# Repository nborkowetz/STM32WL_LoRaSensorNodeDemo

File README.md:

# STM32WL LoRaWAN Sensor Node

Low-power LoRaWAN sensor node based on the **STM32WL55**, originally designed as a prototype platform for distributed water-monitoring applications.

The original goal was not to build a complete water-quality instrument around a fixed set of probes, but to validate the **overall sensing and communication architecture** first: a battery-powered node, generic sensor interfaces, LoRaWAN connectivity, a local gateway and a self-hosted backend.

Water monitoring may involve very different sensors and analog front-ends depending on the quantity being measured. For this reason, the sensing layer is intentionally kept generic while the project focuses on validating the reusable parts of the system.

## Concept

The prototype is intended as a test platform for the complete data path:

```text
Sensor / External AFE
        |
   Analog / RS-485
        |
        v
   STM32WL55 Node
        |
      LoRaWAN
        |
        v
   Dragino Gateway
        |
        v
    ChirpStack
        |
       MQTT
        |
        v
   Backend / Web UI
```

The custom node provides a small set of generic interfaces:

- 3× protected and filtered analog inputs
- RS-485 interface
- Switchable 12 V sensor supply
- STM32WL55 integrated Sub-GHz radio
- USB-UART debug interface
- Battery-powered / low-power operation

Sensor-specific amplification, isolation or signal conditioning can be added externally when required.

This allows the LoRaWAN architecture, power-management strategy and backend to be developed independently from the final choice of water-quality sensors.

## Firmware

The firmware is being developed around a low-power, event-driven architecture with:

- periodic sensor acquisition
- timer-triggered ADC sampling with DMA
- digital filtering / processing
- asynchronous UART / RS-485 communication
- sensor power sequencing and warm-up
- deep-sleep and periodic wake-up
- periodic LoRaWAN uplinks
- UART debug console
- error handling and watchdog supervision

Typical measurement cycle:

```text
Sleep -> Sensor ON -> Warm-up -> Acquire -> Process
      -> Sensor OFF -> LoRaWAN TX (if scheduled) -> Sleep
```

Firmware development and LoRaWAN validation are currently performed using an **STM32WL55 development board**. The custom PCB has been designed but has not yet been fabricated.

Synthetic sensor values can be injected during development to validate payload generation and the complete communication path without depending on the final sensing hardware.

## LoRaWAN Infrastructure

A second goal of the project is to make the LoRaWAN test environment **reproducible and easy to deploy**, instead of relying on a manually configured development machine.

The planned local infrastructure consists of:

- Dragino LoRaWAN gateway
- ChirpStack network server
- Mosquitto MQTT broker
- containerized deployment with Docker Compose
- deployment / provisioning scripts
- Python / FastAPI backend for receiving, storing and visualizing measurements

The intended workflow is:

```text
docker compose up
        |
        v
ChirpStack + MQTT services
        |
        v
Automated provisioning
        |
        v
Gateway / device registration
        |
        v
End-to-end LoRaWAN test
```

Configuration files and scripts are kept in the repository so that the test environment can be recreated from a clean machine with minimal manual configuration.

The backend consumes application data exposed by ChirpStack through MQTT; the STM32 node itself only produces the application payload and remains independent from MQTT or the backend implementation.

## Repository Structure

```text
.
├── Hardware/          # KiCad schematic, PCB and documentation
├── Firmware/          # STM32WL55 firmware
├── Infrastructure/    # ChirpStack / MQTT / Docker deployment
├── Tools/             # Python utilities and provisioning tools
└── README.md
```

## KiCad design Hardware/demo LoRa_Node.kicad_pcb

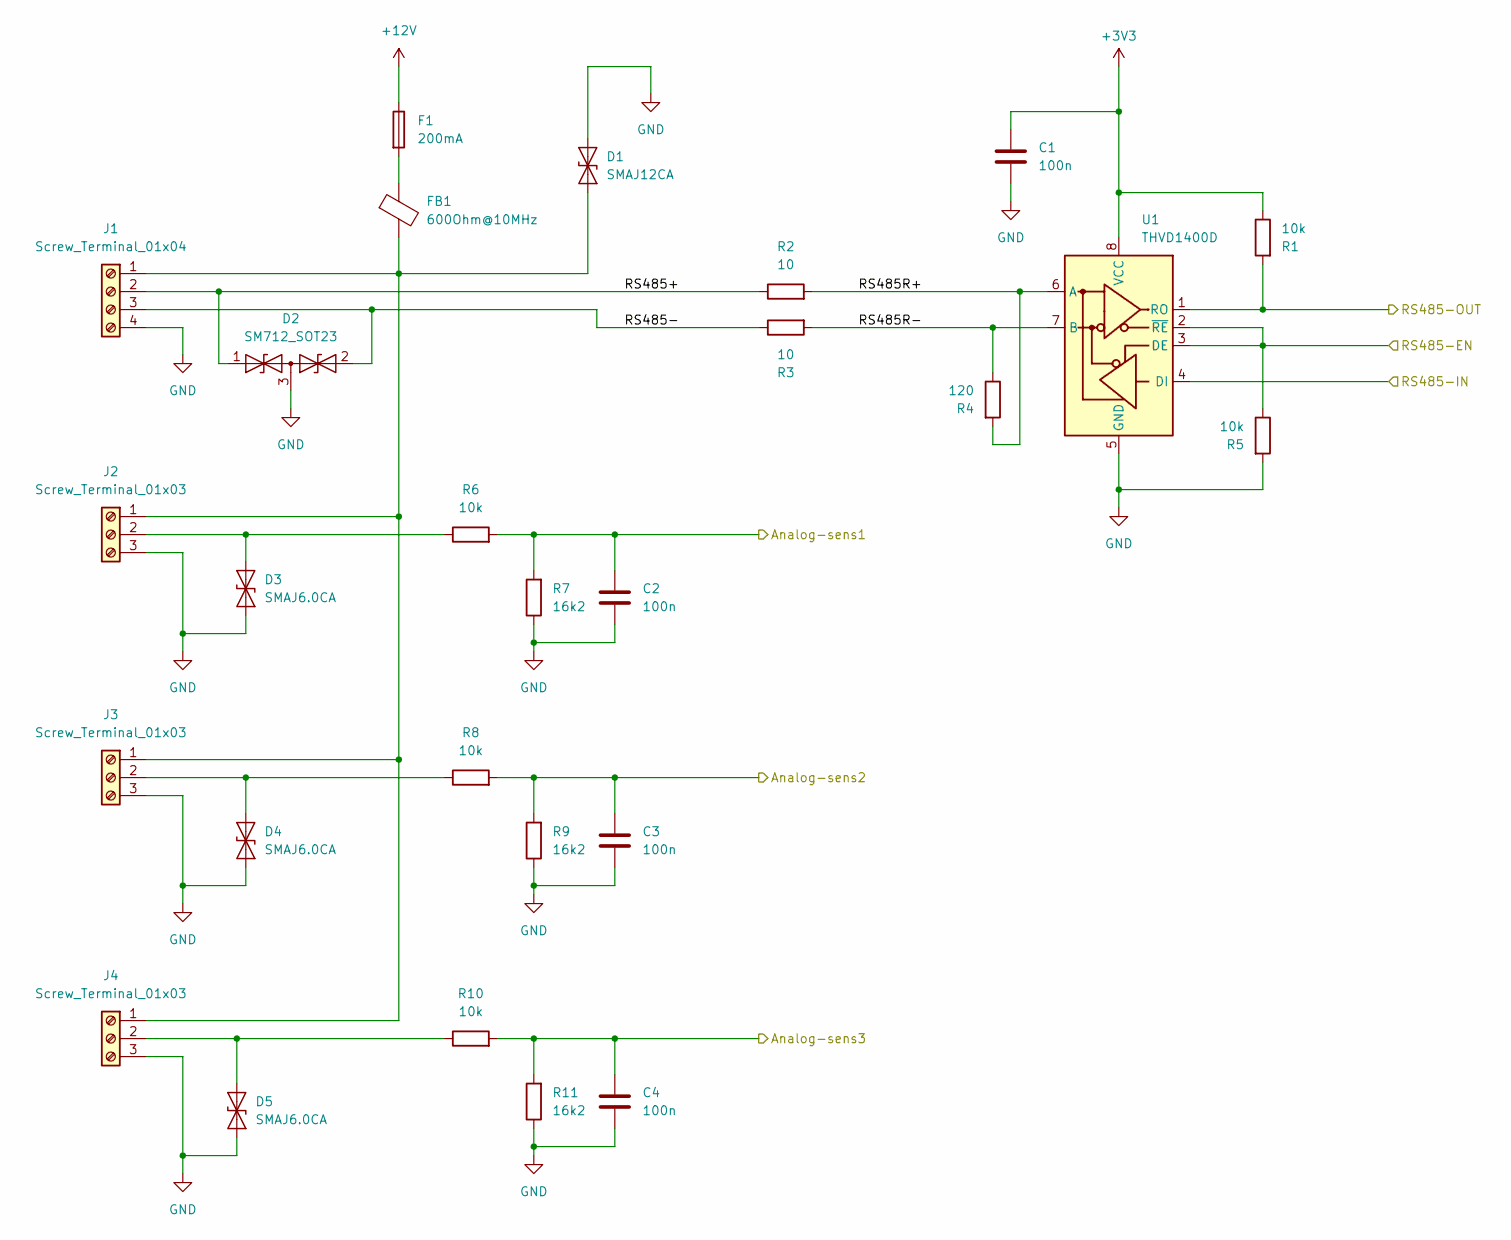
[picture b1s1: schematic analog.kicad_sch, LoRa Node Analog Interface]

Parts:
C1, C2, C3, C4: 100n; C_0603_1608Metric
D1: SMAJ12CA; D_SMA
D2: SM712_SOT23; SOT-23
D3, D4, D5: SMAJ6.0CA; D_SMA
F1: 200mA; Fuse_0805_2012Metric
FB1: 600Ohm@10MHz; L_0603_1608Metric
J1: Screw_Terminal_01x04; TerminalBlock_Phoenix_MKDS-1,5-4-5.08_1x04_P5.08mm_Horizont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
J2, J3, J4: Screw_Terminal_01x03; TerminalBlock_Phoenix_MKDS-1,5-3-5.08_1x03_P5.08mm_Horizont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
R1, R5, R6, R8, R10: 10k; R_0603_1608Metric
R2, R3: 10; R_0603_1608Metric
R4: 120; R_0603_1608Metric
R7, R9, R11: 16k2; R_0603_1608Metric
U1: THVD1400D; SOIC-8_3.9x4.9mm_P1.27mm

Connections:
+3V3: C1.1, R1.1, U1.8 (VCC); also elsewhere on the board
+12V: F1.1; also elsewhere on the board
/MCU/ADC-CH2: C2.1, R6.2, R7.2; also elsewhere on the board
/MCU/ADC-CH3: C3.1, R8.2, R9.2; also elsewhere on the board
/MCU/ADC-CH4: C4.1, R10.2, R11.2; also elsewhere on the board
/MCU/RS485-EN: R5.1, U1.2 (~RE), U1.3 (DE); also elsewhere on the board
/MCU/UART-RX: R1.2, U1.1 (RO); also elsewhere on the board
/MCU/UART-TX: U1.4 (DI); also elsewhere on the board
/analog/RS485+: D2.1 (A1), J1.2, R2.1
/analog/RS485-: D2.2 (A2), J1.3, R3.1
/analog/RS485R+: R2.2, R4.2, U1.6 (A)
/analog/RS485R-: R3.2, R4.1, U1.7 (B)
GND: C1.2, C2.2, C3.2, C4.2, D1.2 (A2), D2.3 (common), D3.1 (A1), D4.1 (A1), D5.1 (A1), J1.4, J2.3, J3.3, J4.3, R5.2, R7.1, R9.1, R11.1, U1.5 (GND); also elsewhere on the board
unnamed: D1.1 (A1), FB1.2, J1.1, J2.1, J3.1, J4.1
unnamed: D3.2 (A2), J2.2, R6.1
unnamed: D4.2 (A2), J3.2, R8.1
unnamed: D5.2 (A2), J4.2, R10.1
unnamed: F1.2, FB1.1

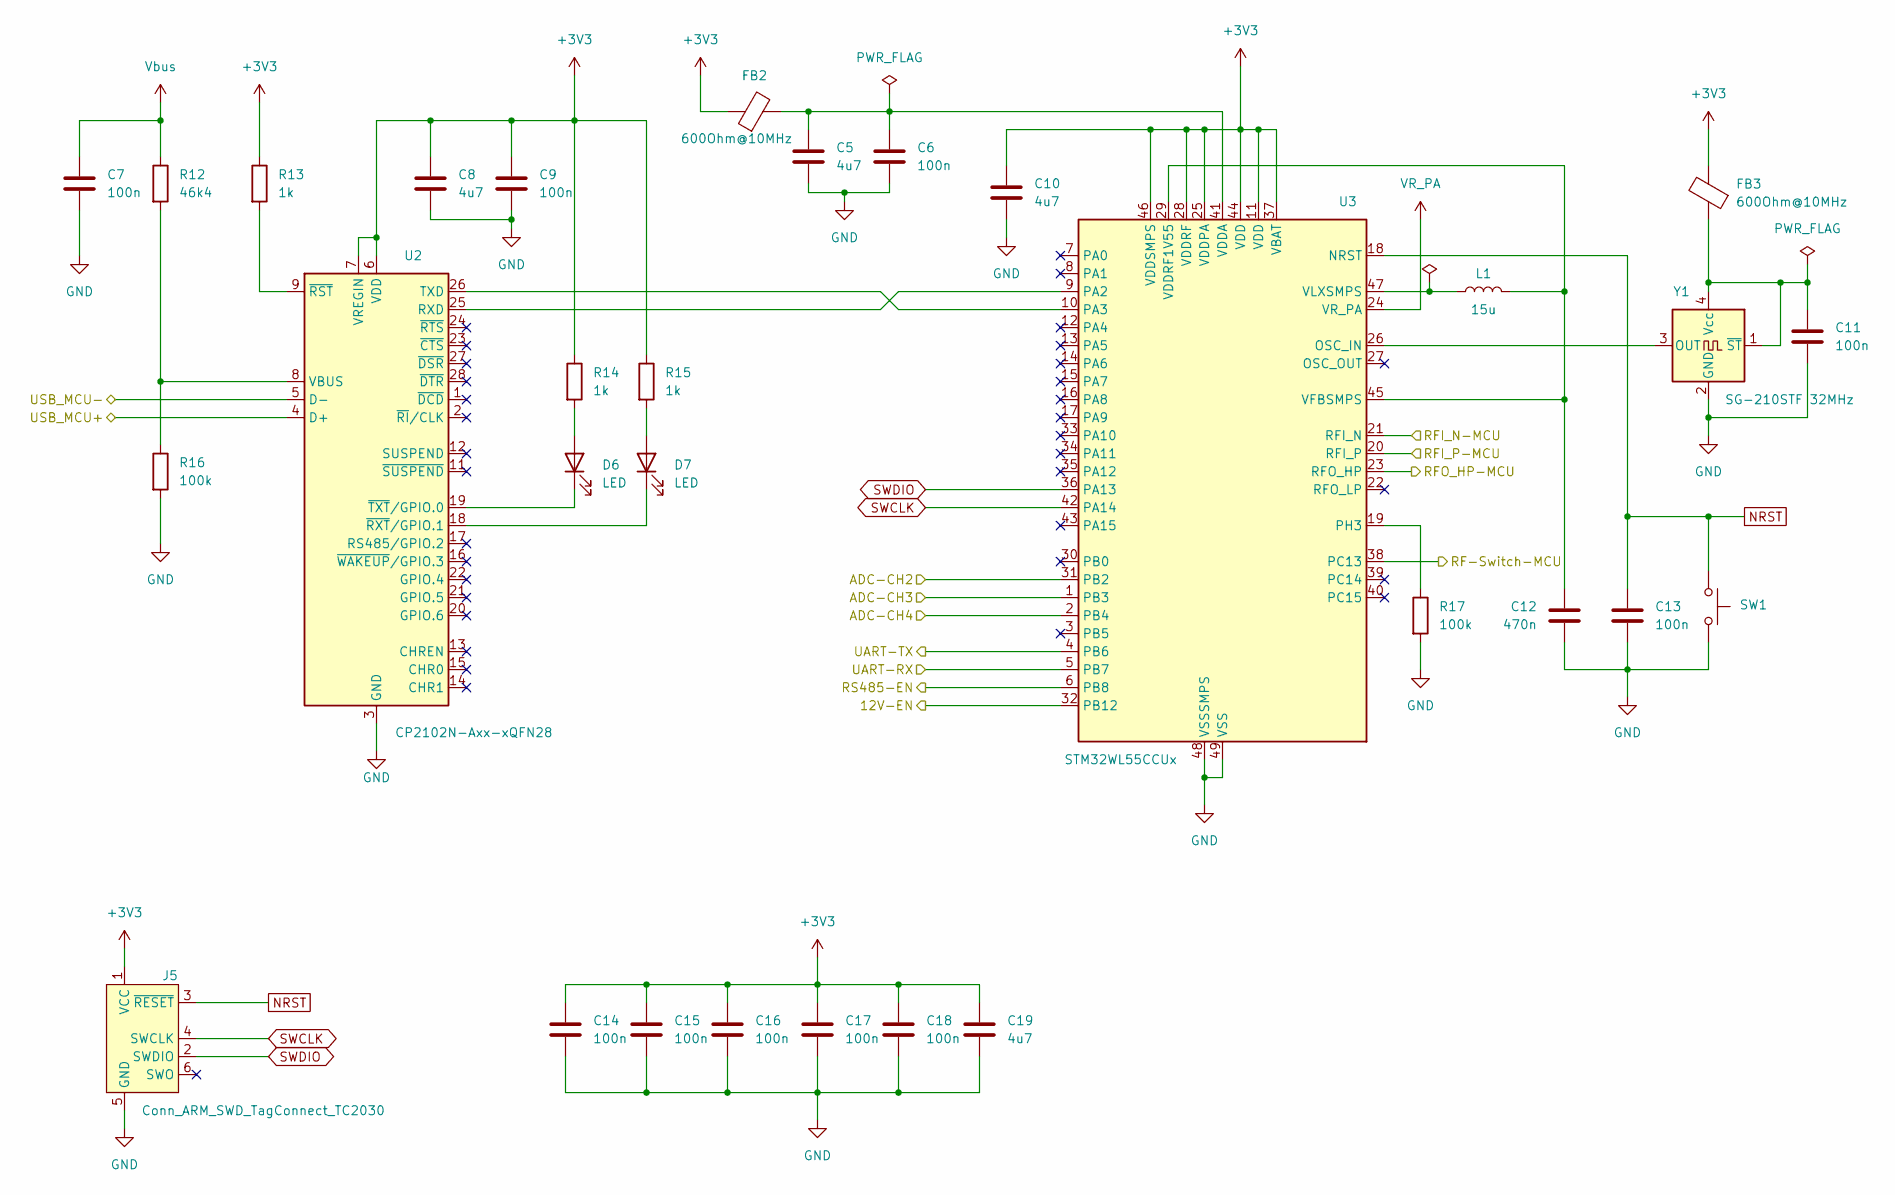
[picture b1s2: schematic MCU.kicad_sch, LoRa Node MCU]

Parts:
C5, C8, C10, C19: 4u7; C_0603_1608Metric
C6, C7, C9, C11, C13, C14, C15, C16, C17, C18: 100n; C_0603_1608Metric
C12: 470n; C_0603_1608Metric
D6, D7: LED; LED_0603_1608Metric
FB2, FB3: 600Ohm@10MHz; L_0603_1608Metric
J5: Conn_ARM_SWD_TagConnect_TC2030; Tag-Connect_TC2030-IDC-NL_2x03_P1.27mm_Vertical
L1: 15u; L_0805_2012Metric
R12: 46k4; R_0603_1608Metric
R13, R14, R15: 1k; R_0603_1608Metric
R16, R17: 100k; R_0603_1608Metric
SW1: SW_Omron_B3FS; SW_SPST_Omron_B3FS-100xP
U2: CP2102N-Axx-xQFN28; QFN-28-1EP_5x5mm_P0.5mm_EP3.35x3.35mm
U3: STM32WL55CCUx; QFN-48-1EP_7x7mm_P0.5mm_EP5.6x5.6mm
Y1: SG-210STF 32MHz; Oscillator_SMD_SeikoEpson_SG210-4Pin_2.5x2.0mm

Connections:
+3V3: C8.1, C9.1, C10.1, C14.1, C15.1, C16.1, C17.1, C18.1, C19.1, FB2.1, FB3.2, J5.1 (VCC), R13.1, R14.1, R15.1, U2.6 (VDD), U2.7 (VREGIN), U3.11 (VDD), U3.25 (VDDPA), U3.28 (VDDRF), U3.37 (VBAT), U3.44 (VDD), U3.46 (VDDSMPS); also elsewhere on the board
/LoRa RF/RF-Switch: U3.38 (PC13); also elsewhere on the board
/LoRa RF/RFI_N: U3.21 (RFI_N); also elsewhere on the board
/LoRa RF/RFI_P: U3.20 (RFI_P); also elsewhere on the board
/LoRa RF/RFO_HP: U3.23 (RFO_HP); also elsewhere on the board
/MCU/12V-EN: U3.32 (PB12); also elsewhere on the board
/MCU/ADC-CH2: U3.31 (PB2); also elsewhere on the board
/MCU/ADC-CH3: U3.1 (PB3); also elsewhere on the board
/MCU/ADC-CH4: U3.2 (PB4); also elsewhere on the board
/MCU/RS485-EN: U3.6 (PB8); also elsewhere on the board
/MCU/UART-RX: U3.5 (PB7); also elsewhere on the board
/MCU/UART-TX: U3.4 (PB6); also elsewhere on the board
/MCU/USB_MCU+: U2.4 (D+); also elsewhere on the board
/MCU/USB_MCU-: U2.5 (D-); also elsewhere on the board
GND: C5.2, C6.2, C7.2, C8.2, C9.2, C10.2, C11.2, C12.2, C13.2, C14.2, C15.2, C16.2, C17.2, C18.2, C19.2, J5.5 (GND), R16.2, R17.2, SW1.1, U2.3 (GND), U2.29 (GND), U3.48 (VSSSMPS), U3.49 (VSS), Y1.2 (GND); also elsewhere on the board
NRST: C13.1, J5.3 (~RESET), SW1.2, U3.18 (NRST)
unnamed: D6.2 (A), R14.2
unnamed: D6.1 (K), U2.19 (~TXT/GPIO.0)
unnamed: D7.2 (A), R15.2
unnamed: D7.1 (K), U2.18 (~RXT/GPIO.1)
unnamed: U2.25 (RXD), U3.9 (PA2)
unnamed: U2.26 (TXD), U3.10 (PA3)
unnamed: R12.2, R16.1, U2.8 (VBUS)
unnamed: R13.2, U2.9 (~RST)
unnamed: U3.26 (OSC_IN), Y1.3 (OUT)
unnamed: R17.1, U3.19 (PH3)
unnamed: C5.1, C6.1, FB2.2, U3.41 (VDDA)
unnamed: C12.1, L1.2, U3.29 (VDDRF1V55), U3.45 (VFBSMPS)
unnamed: L1.1, U3.47 (VLXSMPS)
unnamed: C11.1, FB3.1, Y1.1 (~ST), Y1.4 (Vcc)
SWCLK: J5.4 (SWCLK), U3.42 (PA14)
SWDIO: J5.2 (SWDIO), U3.36 (PA13)
VR_PA: U3.24 (VR_PA); also elsewhere on the board
Vbus: C7.1, R12.1; also elsewhere on the board

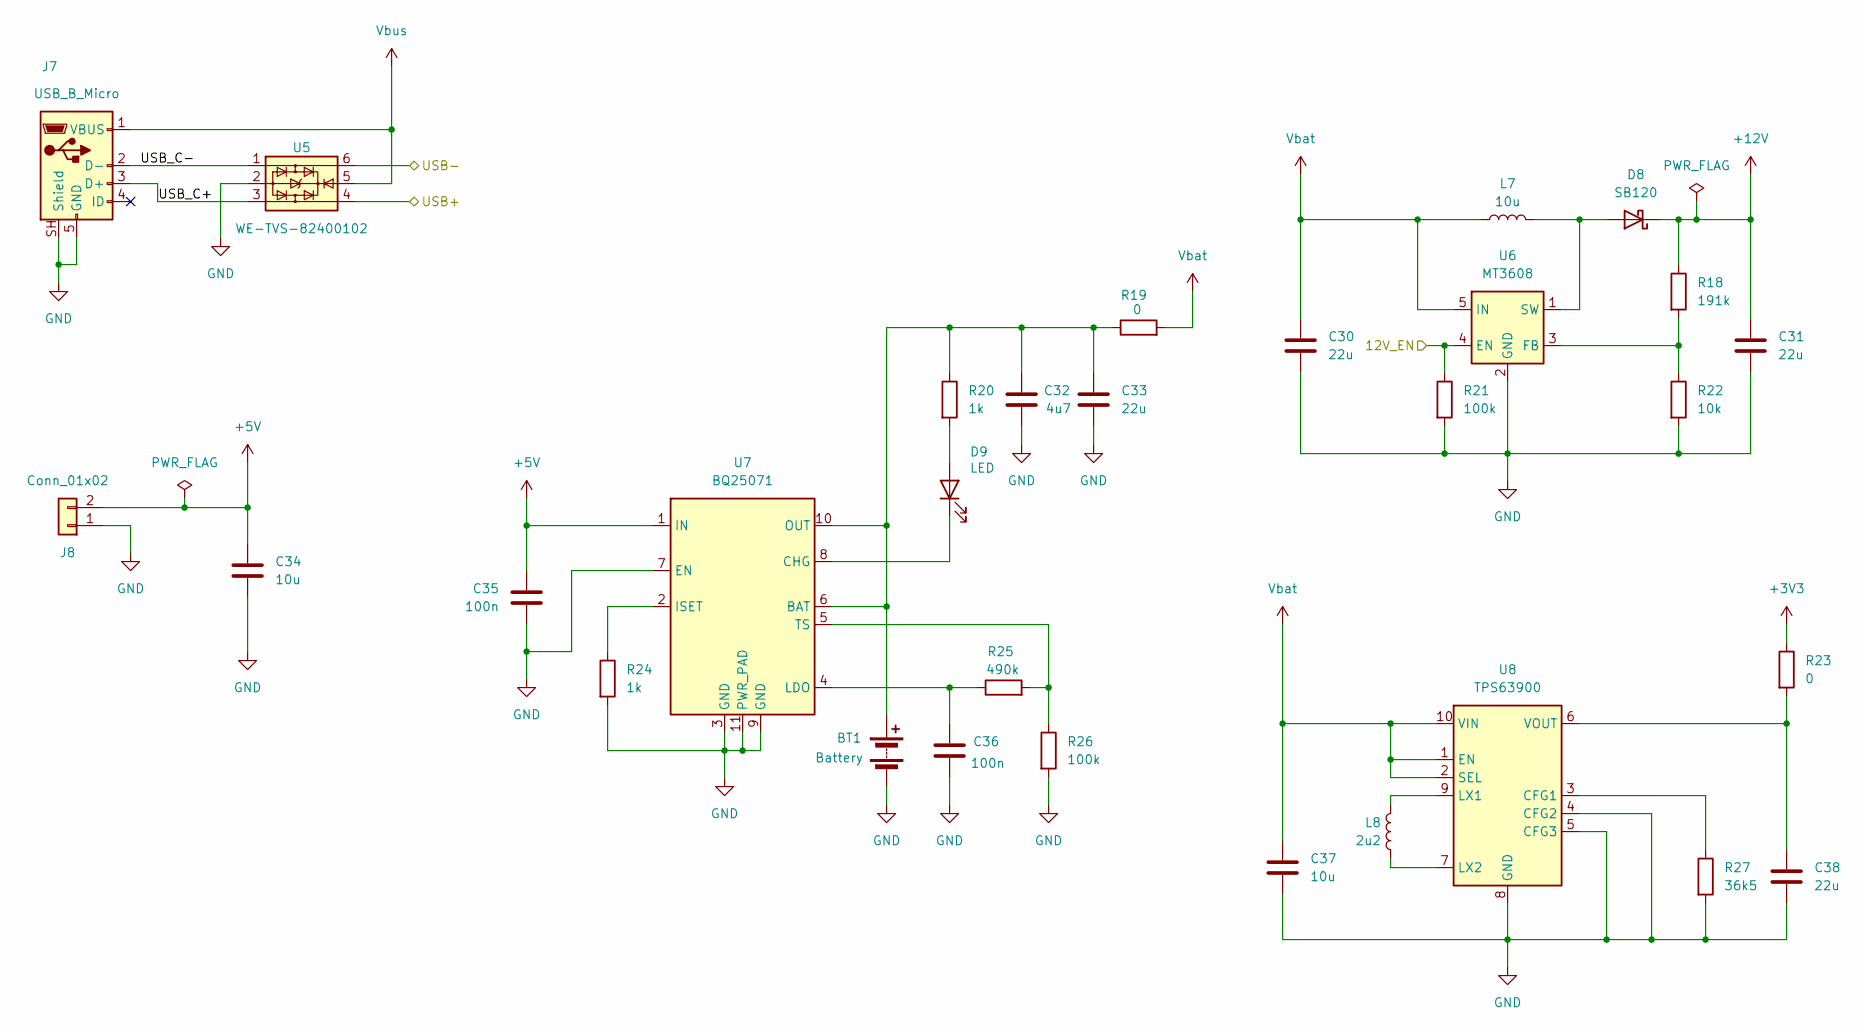
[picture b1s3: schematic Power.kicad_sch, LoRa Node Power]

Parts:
BT1: Battery; PhoenixContact_MCV_1,5_2-G-3.81_1x02_P3.81mm_Vertical
C30, C31, C33, C38: 22u; C_0603_1608Metric
C32: 4u7; C_0603_1608Metric
C34, C37: 10u; C_0603_1608Metric
C35, C36: 100n; C_0603_1608Metric
D8: SB120; D_SOD-128
D9: LED; LED_0603_1608Metric
J7: USB_B_Micro; Amphenol usb micro connector
J8: Conn_01x02; TerminalBlock_TE_282834-2_1x02_P2.54mm_Horizontal
L7: 10u; L_0805_2012Metric
L8: 2u2; L_0805_2012Metric
R18: 191k; R_0603_1608Metric
R19, R23: 0; R_0603_1608Metric
R20, R24: 1k; R_0603_1608Metric
R21, R26: 100k; R_0603_1608Metric
R22: 10k; R_0603_1608Metric
R25: 490k; R_0603_1608Metric
R27: 36k5; R_0603_1608Metric
U5: WE-TVS-82400102; SOT-23-6_Handsoldering
U6: MT3608; SOT-23-6
U7: BQ25071; WSON-10-1EP_2x3mm_P0.5mm_EP0.84x2.4mm_ThermalVias
U8: TPS63900; WSON-10-1EP_2.5x2.5mm_P0.5mm_EP1.2x2mm_ThermalVias

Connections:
+3V3: R23.1; also elsewhere on the board
+5V: C34.1, C35.1, J8.2, U7.1 (IN)
+12V: C31.1, D8.1 (K), R18.1; also elsewhere on the board
/MCU/12V-EN: R21.1, U6.4 (EN); also elsewhere on the board
/MCU/USB_MCU+: U5.4; also elsewhere on the board
/MCU/USB_MCU-: U5.6; also elsewhere on the board
/Power/USB_C+: J7.3 (D+), U5.3
/Power/USB_C-: J7.2 (D-), U5.1
GND: BT1.2 (-), C30.2, C31.2, C32.2, C33.2, C34.2, C35.2, C36.2, C37.2, C38.2, J7.5 (GND), J7.SH (Shield), J8.1, R21.2, R22.2, R24.2, R26.2, R27.2, U5.2, U6.2 (GND), U7.3 (GND), U7.7 (EN), U7.9 (GND), U7.11 (PWR_PAD), U8.4 (CFG2), U8.5 (CFG3), U8.8 (GND), U8.11 (GND); also elsewhere on the board
unnamed: BT1.1 (+), C32.1, C33.1, R19.1, R20.1, U7.6 (BAT), U7.10 (OUT)
unnamed: D8.2 (A), L7.2, U6.1 (SW)
unnamed: D9.2 (A), R20.2
unnamed: D9.1 (K), U7.8 (CHG)
unnamed: R18.2, R22.1, U6.3 (FB)
unnamed: R24.1, U7.2 (ISET)
unnamed: C36.1, R25.1, U7.4 (LDO)
unnamed: R25.2, R26.1, U7.5 (TS)
unnamed: R27.1, U8.3 (CFG1)
unnamed: L8.1, U8.9 (LX1)
unnamed: L8.2, U8.7 (LX2)
unnamed: C38.1, R23.2, U8.6 (VOUT)
Vbat: C30.1, C37.1, L7.1, R19.2, U6.5 (IN), U8.1 (EN), U8.2 (SEL), U8.10 (VIN)
Vbus: J7.1 (VBUS), U5.5; also elsewhere on the board

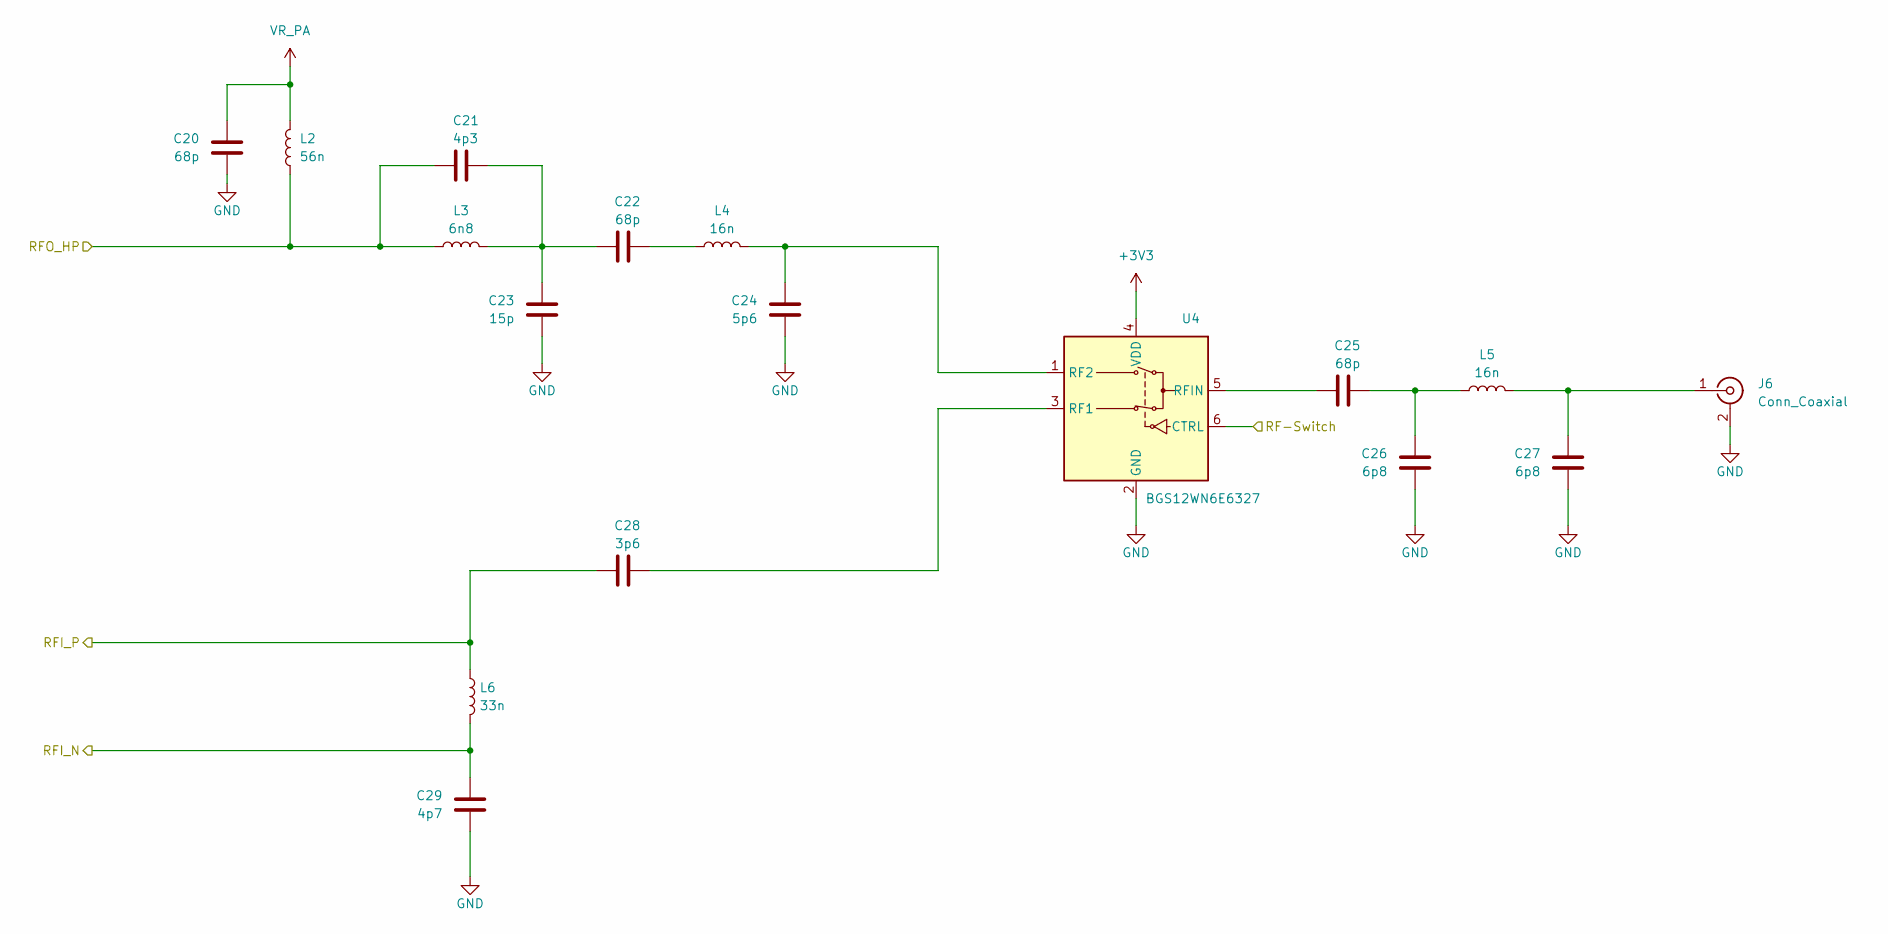
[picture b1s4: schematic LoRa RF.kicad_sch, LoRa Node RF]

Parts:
C20, C22, C25: 68p; C_0603_1608Metric
C21: 4p3; C_0603_1608Metric
C23: 15p; C_0603_1608Metric
C24: 5p6; C_0603_1608Metric
C26, C27: 6p8; C_0603_1608Metric
C28: 3p6; C_0603_1608Metric
C29: 4p7; C_0603_1608Metric
J6: Conn_Coaxial; BNC_TEConnectivity_1478035_Horizontal
L2: 56n; L_0603_1608Metric
L3: 6n8; L_0603_1608Metric
L4, L5: 16n; L_0603_1608Metric
L6: 33n; L_0603_1608Metric
U4: BGS12WN6E6327; Infineon_PG-TSNP-6-10_0.7x1.1mm_0.7x1.1mm_P0.4mm

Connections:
+3V3: U4.4 (VDD); also elsewhere on the board
/LoRa RF/RF-Switch: U4.6 (CTRL); also elsewhere on the board
/LoRa RF/RFI_N: C29.1, L6.2; also elsewhere on the board
/LoRa RF/RFI_P: C28.1, L6.1; also elsewhere on the board
/LoRa RF/RFO_HP: C21.2, L2.1, L3.1; also elsewhere on the board
GND: C20.2, C23.2, C24.2, C26.2, C27.2, C29.2, J6.2 (Ext), U4.2 (GND); also elsewhere on the board
unnamed: C21.1, C22.1, C23.1, L3.2
unnamed: C22.2, L4.1
unnamed: C25.2, C26.1, L5.1
unnamed: C27.1, J6.1 (In), L5.2
unnamed: C28.2, U4.3 (RF1)
unnamed: C24.1, L4.2, U4.1 (RF2)
unnamed: C25.1, U4.5 (RFIN)
VR_PA: C20.1, L2.2; also elsewhere on the board

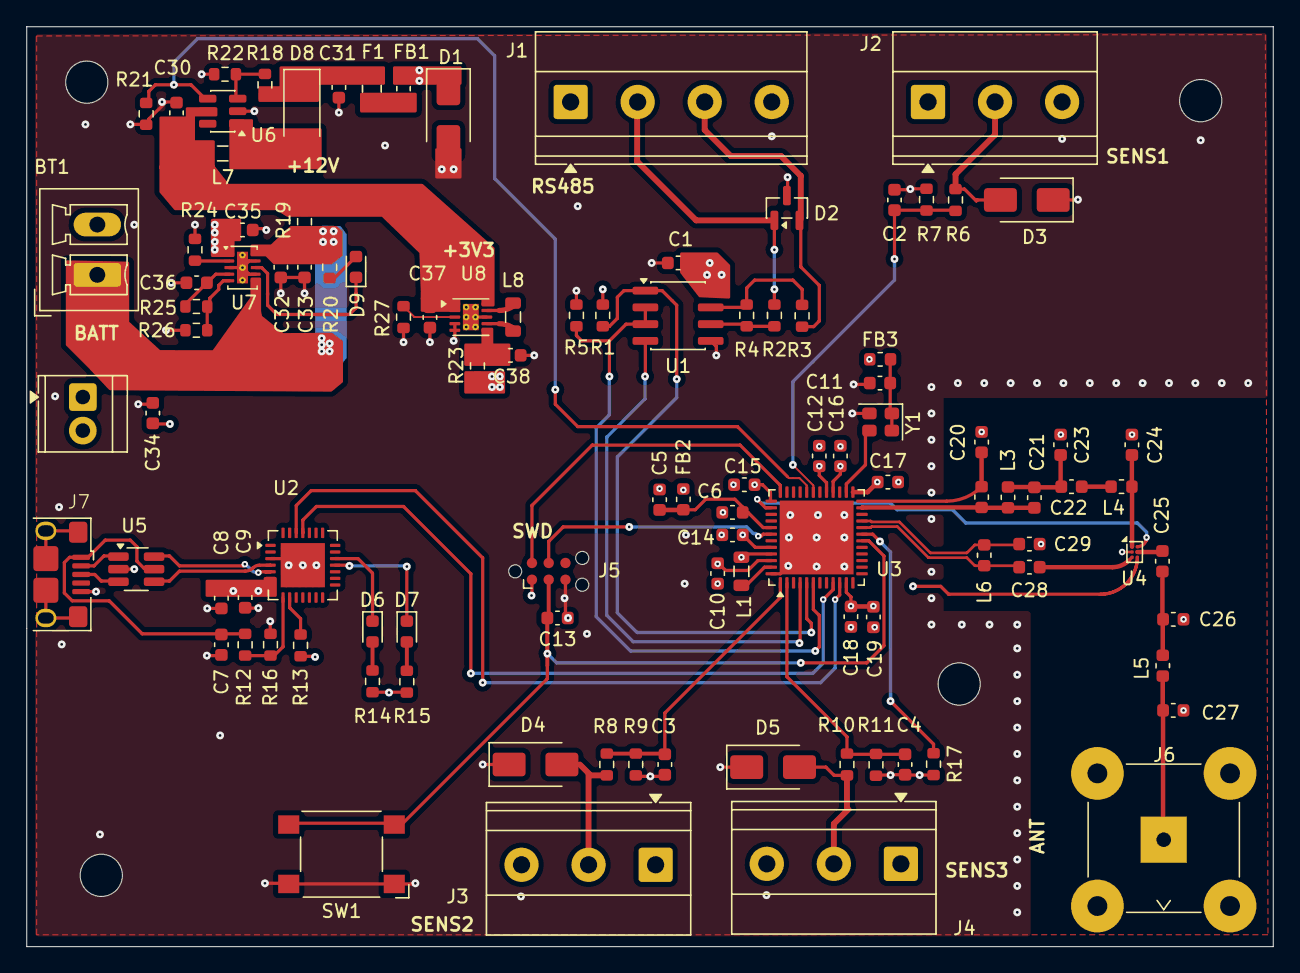
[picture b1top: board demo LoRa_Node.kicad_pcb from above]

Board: 4 copper layers, 94.5 x 69.7 mm, 105 parts (0 on the bottom side), 67 nets.
